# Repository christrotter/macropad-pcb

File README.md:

# macropad-pcb
Are you using the [Arcboard-pcb-inator](https://github.com/christrotter/mk18-pcb)?  And you need more keyyyyys?  Arranged in a 2 row / 4 col layout?

# features
We are taking 8 individual Cyboard key pcbs, merging them into one FFC output.

- 8x 0.3mm 8-pin FFC Type-A -> 1x 0.5mm 16-pin FFC Type-A
- the main FFC connector is a mirror of that on the [Arcboard-pcb-inator](https://github.com/christrotter/mk18-pcb)
- M3 mounting holes
- test points
- cable slots
- that is all

# schematic

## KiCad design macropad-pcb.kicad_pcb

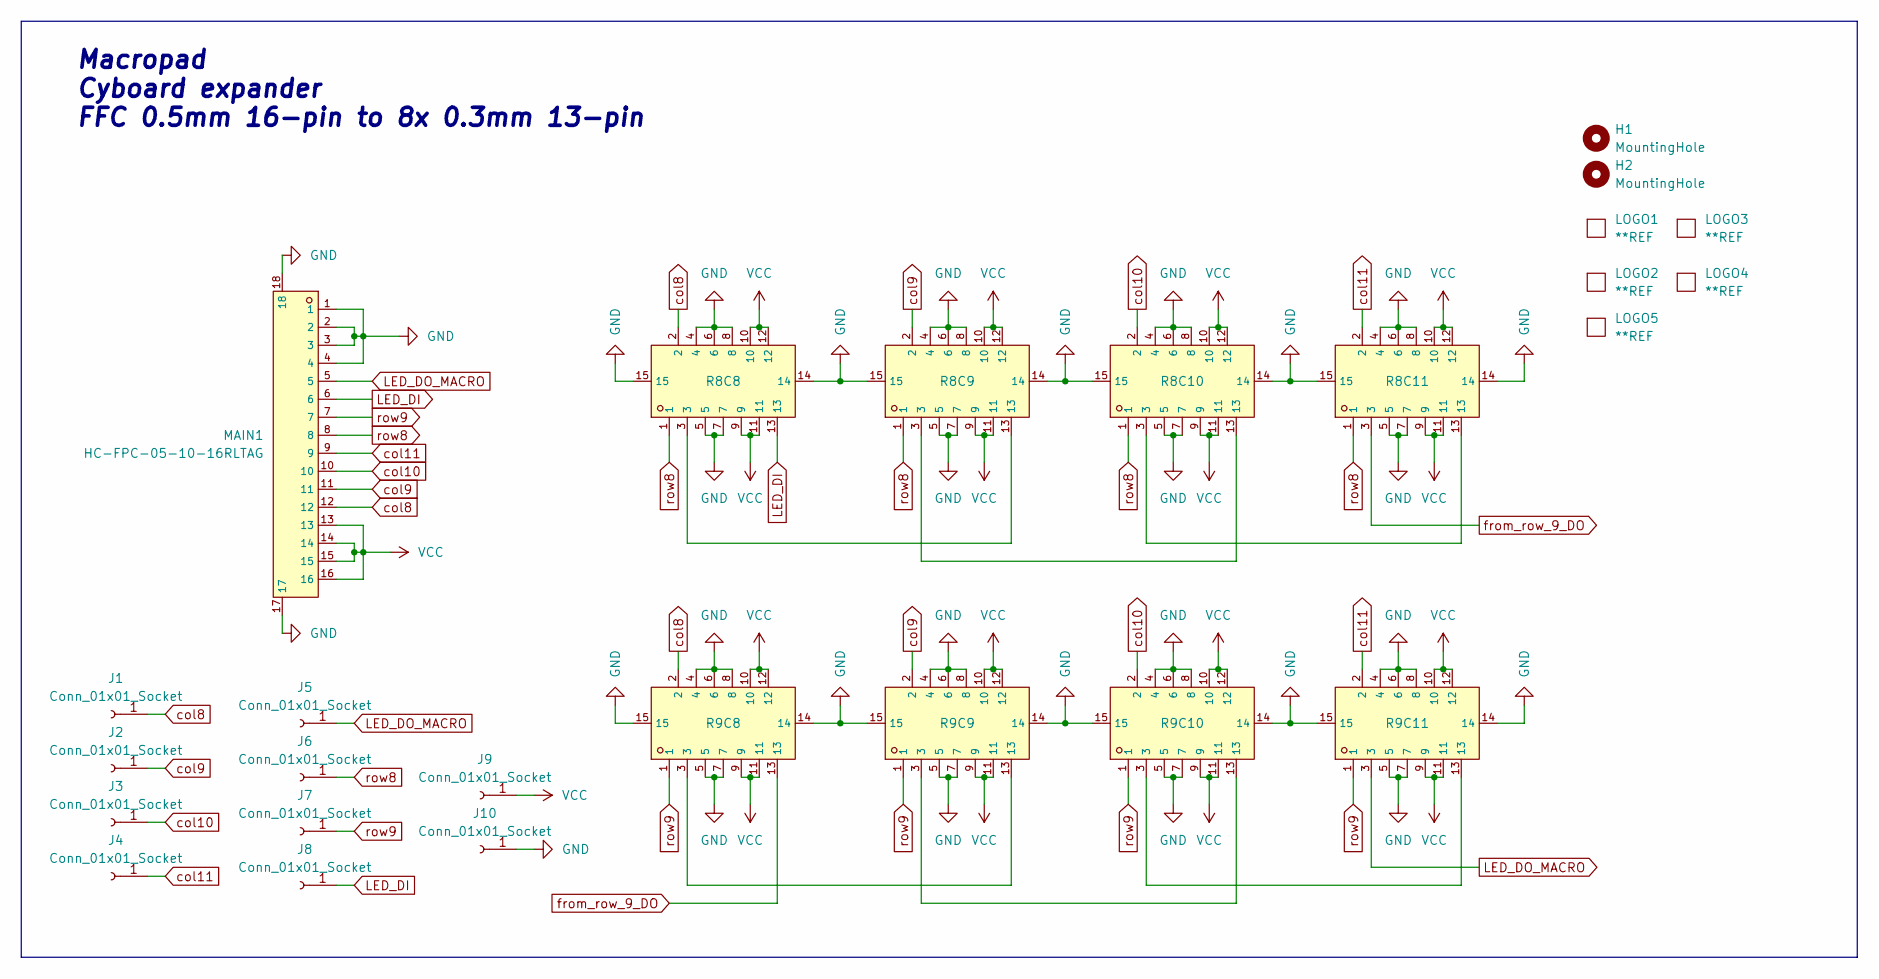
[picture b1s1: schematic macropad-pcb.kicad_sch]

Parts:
H1, H2: MountingHole; MountingHole_3mm_Pad_Via
J1, J2, J3, J4, J5, J6, J7, J8, J9, J10: Conn_01x01_Socket; PinHeader_1x01_P2.54mm_Vertical
LOGO1, LOGO3: **REF; awesome-logo
LOGO2: **REF; qmk-lite
LOGO4: **REF; macropad-pcb-qr-10mm
LOGO5: **REF; cyboard-logo-10mm
MAIN1: HC-FPC-05-10-16RLTAG; FPC-SMD_16P-P0.50_HCTL_HC-FPC-05-10-16RLTAG; LCSC C5213735
R8C8, R8C9, R8C10, R8C11, R9C8, R9C9, R9C10, R9C11: FH26W-13S-0_3SHW(60); FPC-SMD_FH26W-13S-0.3SHW-60; LCSC C424653

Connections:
GND: J10.1, MAIN1.1, MAIN1.2, MAIN1.3, MAIN1.4, MAIN1.17, MAIN1.18, R8C8.4, R8C8.5, R8C8.6, R8C8.7, R8C8.8, R8C8.14, R8C8.15, R8C9.4, R8C9.5, R8C9.6, R8C9.7, R8C9.8, R8C9.14, R8C9.15, R8C10.4, R8C10.5, R8C10.6, R8C10.7, R8C10.8, R8C10.14, R8C10.15, R8C11.4, R8C11.5, R8C11.6, R8C11.7, R8C11.8, R8C11.14, R8C11.15, R9C8.4, R9C8.5, R9C8.6, R9C8.7, R9C8.8, R9C8.14, R9C8.15, R9C9.4, R9C9.5, R9C9.6, R9C9.7, R9C9.8, R9C9.14, R9C9.15, R9C10.4, R9C10.5, R9C10.6, R9C10.7, R9C10.8, R9C10.14, R9C10.15, R9C11.4, R9C11.5, R9C11.6, R9C11.7, R9C11.8, R9C11.14, R9C11.15
LED_DI: J8.1, MAIN1.6, R8C8.13
LED_DO_MACRO: J5.1, MAIN1.5, R9C11.3
unnamed: R8C8.3, R8C9.13
unnamed: R8C10.3, R8C11.13
unnamed: R8C9.3, R8C10.13
unnamed: R9C8.3, R9C9.13
unnamed: R9C10.3, R9C11.13
unnamed: R9C9.3, R9C10.13
VCC: J9.1, MAIN1.13, MAIN1.14, MAIN1.15, MAIN1.16, R8C8.9, R8C8.10, R8C8.11, R8C8.12, R8C9.9, R8C9.10, R8C9.11, R8C9.12, R8C10.9, R8C10.10, R8C10.11, R8C10.12, R8C11.9, R8C11.10, R8C11.11, R8C11.12, R9C8.9, R9C8.10, R9C8.11, R9C8.12, R9C9.9, R9C9.10, R9C9.11, R9C9.12, R9C10.9, R9C10.10, R9C10.11, R9C10.12, R9C11.9, R9C11.10, R9C11.11, R9C11.12
col8: J1.1, MAIN1.12, R8C8.2, R9C8.2
col9: J2.1, MAIN1.11, R8C9.2, R9C9.2
col10: J3.1, MAIN1.10, R8C10.2, R9C10.2
col11: J4.1, MAIN1.9, R8C11.2, R9C11.2
from_row_9_DO: R8C11.3, R9C8.13
row8: J6.1, MAIN1.8, R8C8.1, R8C9.1, R8C10.1, R8C11.1
row9: J7.1, MAIN1.7, R9C8.1, R9C9.1, R9C10.1, R9C11.1

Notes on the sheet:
Macropad Cyboard expander FFC 0.5mm 16-pin to 8x 0.3mm 13-pin

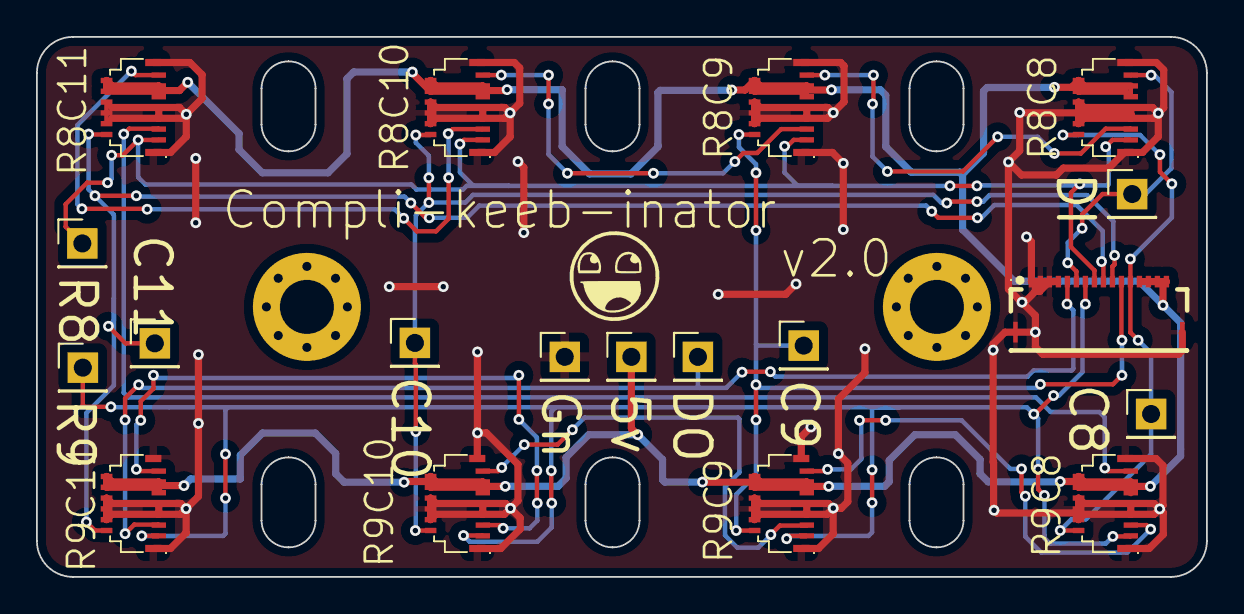
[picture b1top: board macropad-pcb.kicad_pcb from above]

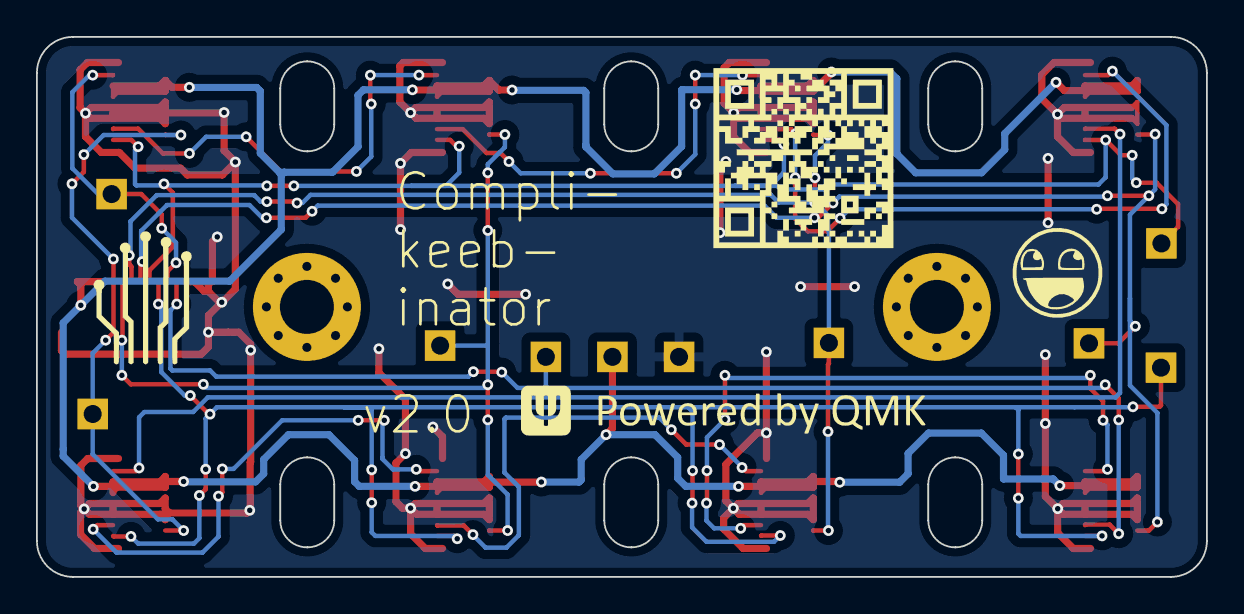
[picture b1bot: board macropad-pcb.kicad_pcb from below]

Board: 2 copper layers, 65.0 x 30.0 mm, 26 parts (4 on the bottom side), 17 nets.

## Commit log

2024-01-01 getting v1.0 files added
2024-01-07 adding readme and doof
2024-01-07 adding more images, updating readme
2024-01-28 rev2 ready for sleeping on
2024-01-28 more updates to the board, waiting on cyboard logo
2024-01-28 updating images
2024-01-28 updated w. flipped main connectior
2024-01-28 added cyboard logo
2024-01-28 added cyboard logo, placed order
2024-01-28 updating the funny image
2024-01-28 updating readme
